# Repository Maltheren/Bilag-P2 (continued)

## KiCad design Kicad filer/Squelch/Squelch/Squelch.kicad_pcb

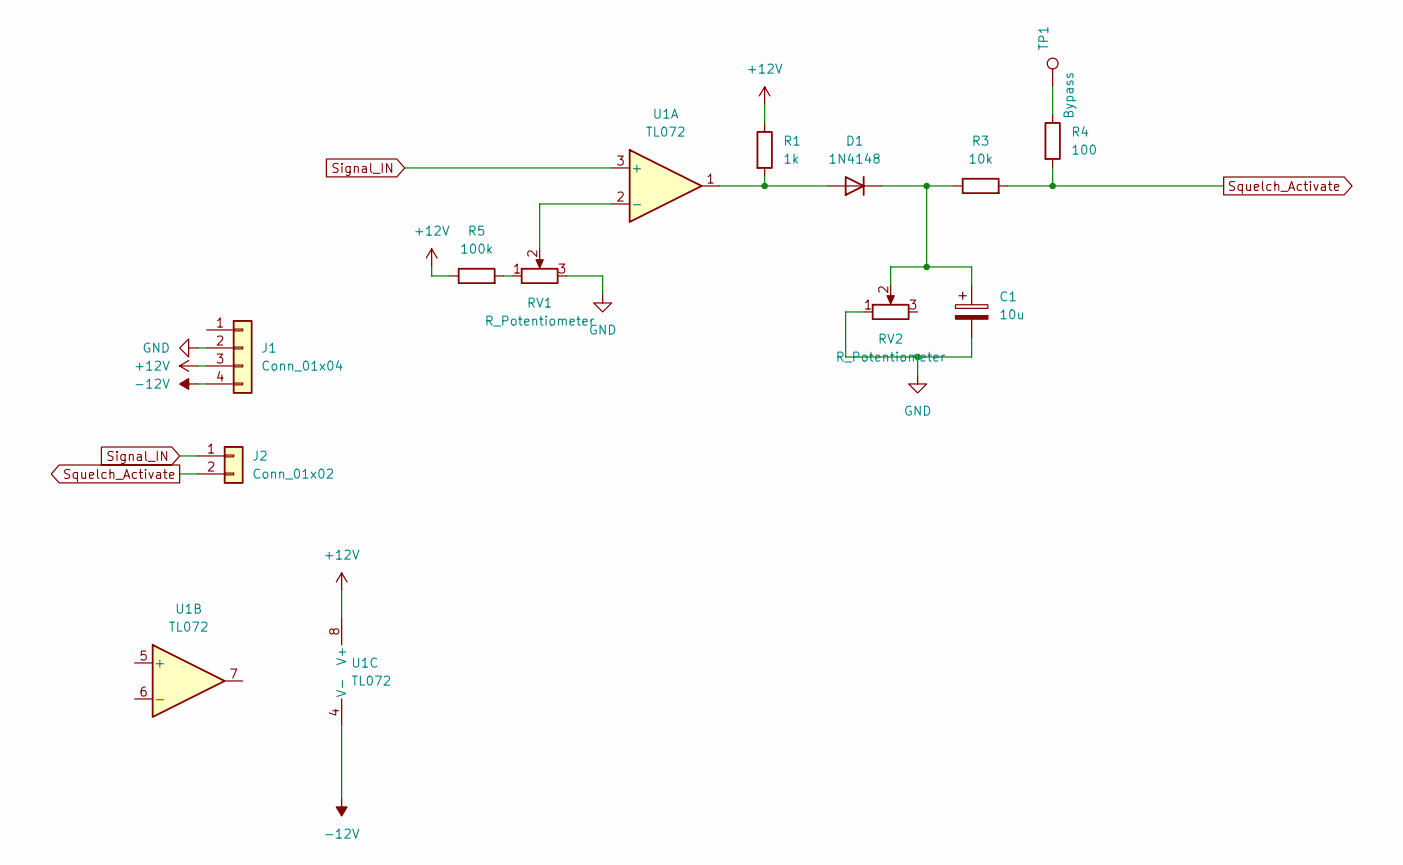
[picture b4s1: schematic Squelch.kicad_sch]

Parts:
C1: 10u; CP_Axial_L10.0mm_D6.0mm_P15.00mm_Horizontal
D1: 1N4148; D_DO-35_SOD27_P7.62mm_Horizontal
J1: Conn_01x04; PinHeader_1x04_P2.54mm_Vertical
J2: Conn_01x02; PinHeader_1x02_P2.54mm_Vertical
R1: 1k; R_Axial_DIN0207_L6.3mm_D2.5mm_P10.16mm_Horizontal
R3: 10k; R_Axial_DIN0207_L6.3mm_D2.5mm_P10.16mm_Horizontal
R4: 100; R_Axial_DIN0207_L6.3mm_D2.5mm_P10.16mm_Horizontal
R5: 100k; R_Axial_DIN0207_L6.3mm_D2.5mm_P10.16mm_Horizontal
RV1, RV2: R_Potentiometer; Potentiometer_Bourns_3386P_Vertical
TP1: Bypass; PinHeader_1x01_P2.54mm_Vertical
U1: TL072; DIP-8_W7.62mm_LongPads

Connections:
+12V: J1.3, R1.1, R5.1, U1.8 (V+)
-12V: J1.4, U1.4 (V-)
GND: C1.2, J1.2, RV1.3, RV2.1
unnamed: D1.2 (A), R1.2, U1.1
unnamed: C1.1, D1.1 (K), R3.1, RV2.2
unnamed: R4.1, TP1.1
unnamed: R5.2, RV1.1
unnamed: RV1.2, U1.2 (-)
Signal_IN: J2.1, U1.3 (+)
Squelch_Activate: J2.2, R3.2, R4.2

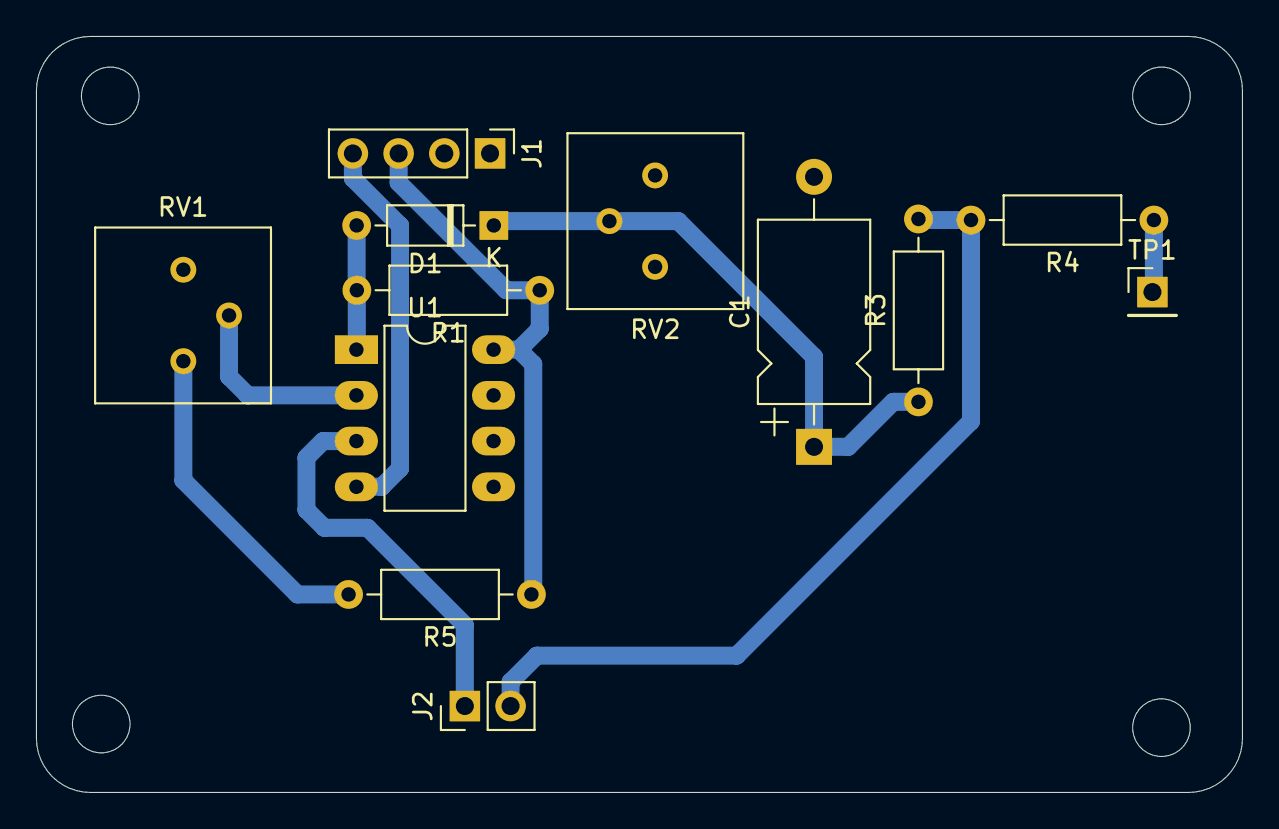
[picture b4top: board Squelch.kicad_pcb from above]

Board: 2 copper layers, 67.0 x 42.0 mm, 12 parts (0 on the bottom side), 10 nets.

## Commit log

2024-05-22 færdige bilag v1
2024-05-22 Alle ændringer v1
2024-05-23 PDF filer
2024-06-12 Update HAL.h
    Fjernede grimme ord
